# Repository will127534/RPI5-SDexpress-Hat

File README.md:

# RPI5-SDexpress-Hat

Basically a clone from my [CFE Hat](https://github.com/will127534/RPI5-CFE-Hat) project and just changed the CFexpress Socket to SDexpress.  

Hardware-wise SDexpress requires additional 1.8V DC-DC and I'm using PAM2306 here, note that you can see in the photo the FB resistors are actually missing, the board is design for the adjustable version but this chip has 1.8V/3.3V fixed output variant and in that case you can put the 0 ohm resistor and that's what I have in the photo.  

Raspberry Pi's software-wise it is the exact same as CFE hat, the FW on MCU is slightly different that for layout reasons I shifted the LED output to another port and the FW in HEX is in this repo. See this [Youtube](https://youtu.be/_K-CHcIZxTY) for the HAT in action (automount/manual unmount).

[Interactive BOM](https://htmlpreview.github.io/?https://github.com/will127534/RPI5-SDexpress-Hat/blob/main/bom/ibom.html) [(provided by InteractiveHtmlBom)
](https://github.com/openscopeproject/InteractiveHtmlBom) 

### Random notes
In general, I don't really see a point of using microSD express card: If you need external storage, M.2 SSD is cheaper; If you need removable storage, M.2 SSD in CFexpress Type B is cheaper.  

microSD express reading speed is indeed faster then microSD card, however it's writing speed is more about the same as high-end microSD express card (160~200MB/s). Now you might see some microSD express advertise for >200MB/s writing speed, but that is not *sustained* performance, similar to how NVMe SSD works, some microSD express have pSLC cache for higher burst write speed. So it make sense as a gaming storage but I don't see the point for camera recording or any type of high speed recording device given the pricing comparing to standard high-end microSD card / USB flash or M.2 SSDs. I actually waited for a while to see if there are cheaper options other then the Nintendo branded one but there is none. I'm guessing that there is a physical/power limit on how many NAND channel you can fit in microSD card format, which limits the sustained write performance because that is based on RAW NAND speed.  

Thermal-wise with and without external fan doesn't change the performance during the stress test that last for an hour, it does get a little bit warm but it is not hot at all so that is some good news. Something I didn't expect though is that there aren't a lot of options for the socket either, and there is no self-ejection options out there currently and it actually took me a lot of force to pull the card out.  For more card specific testing, see here for more: [https://github.com/geerlingguy/raspberry-pi-pcie-devices/issues/745](https://github.com/geerlingguy/raspberry-pi-pcie-devices/issues/745)

One last note: I won't do PCBA for this board because microSD express card is not there(Cost/Performance/Prevalent) yet, but this project is in MIT license so do whatever you want with this.

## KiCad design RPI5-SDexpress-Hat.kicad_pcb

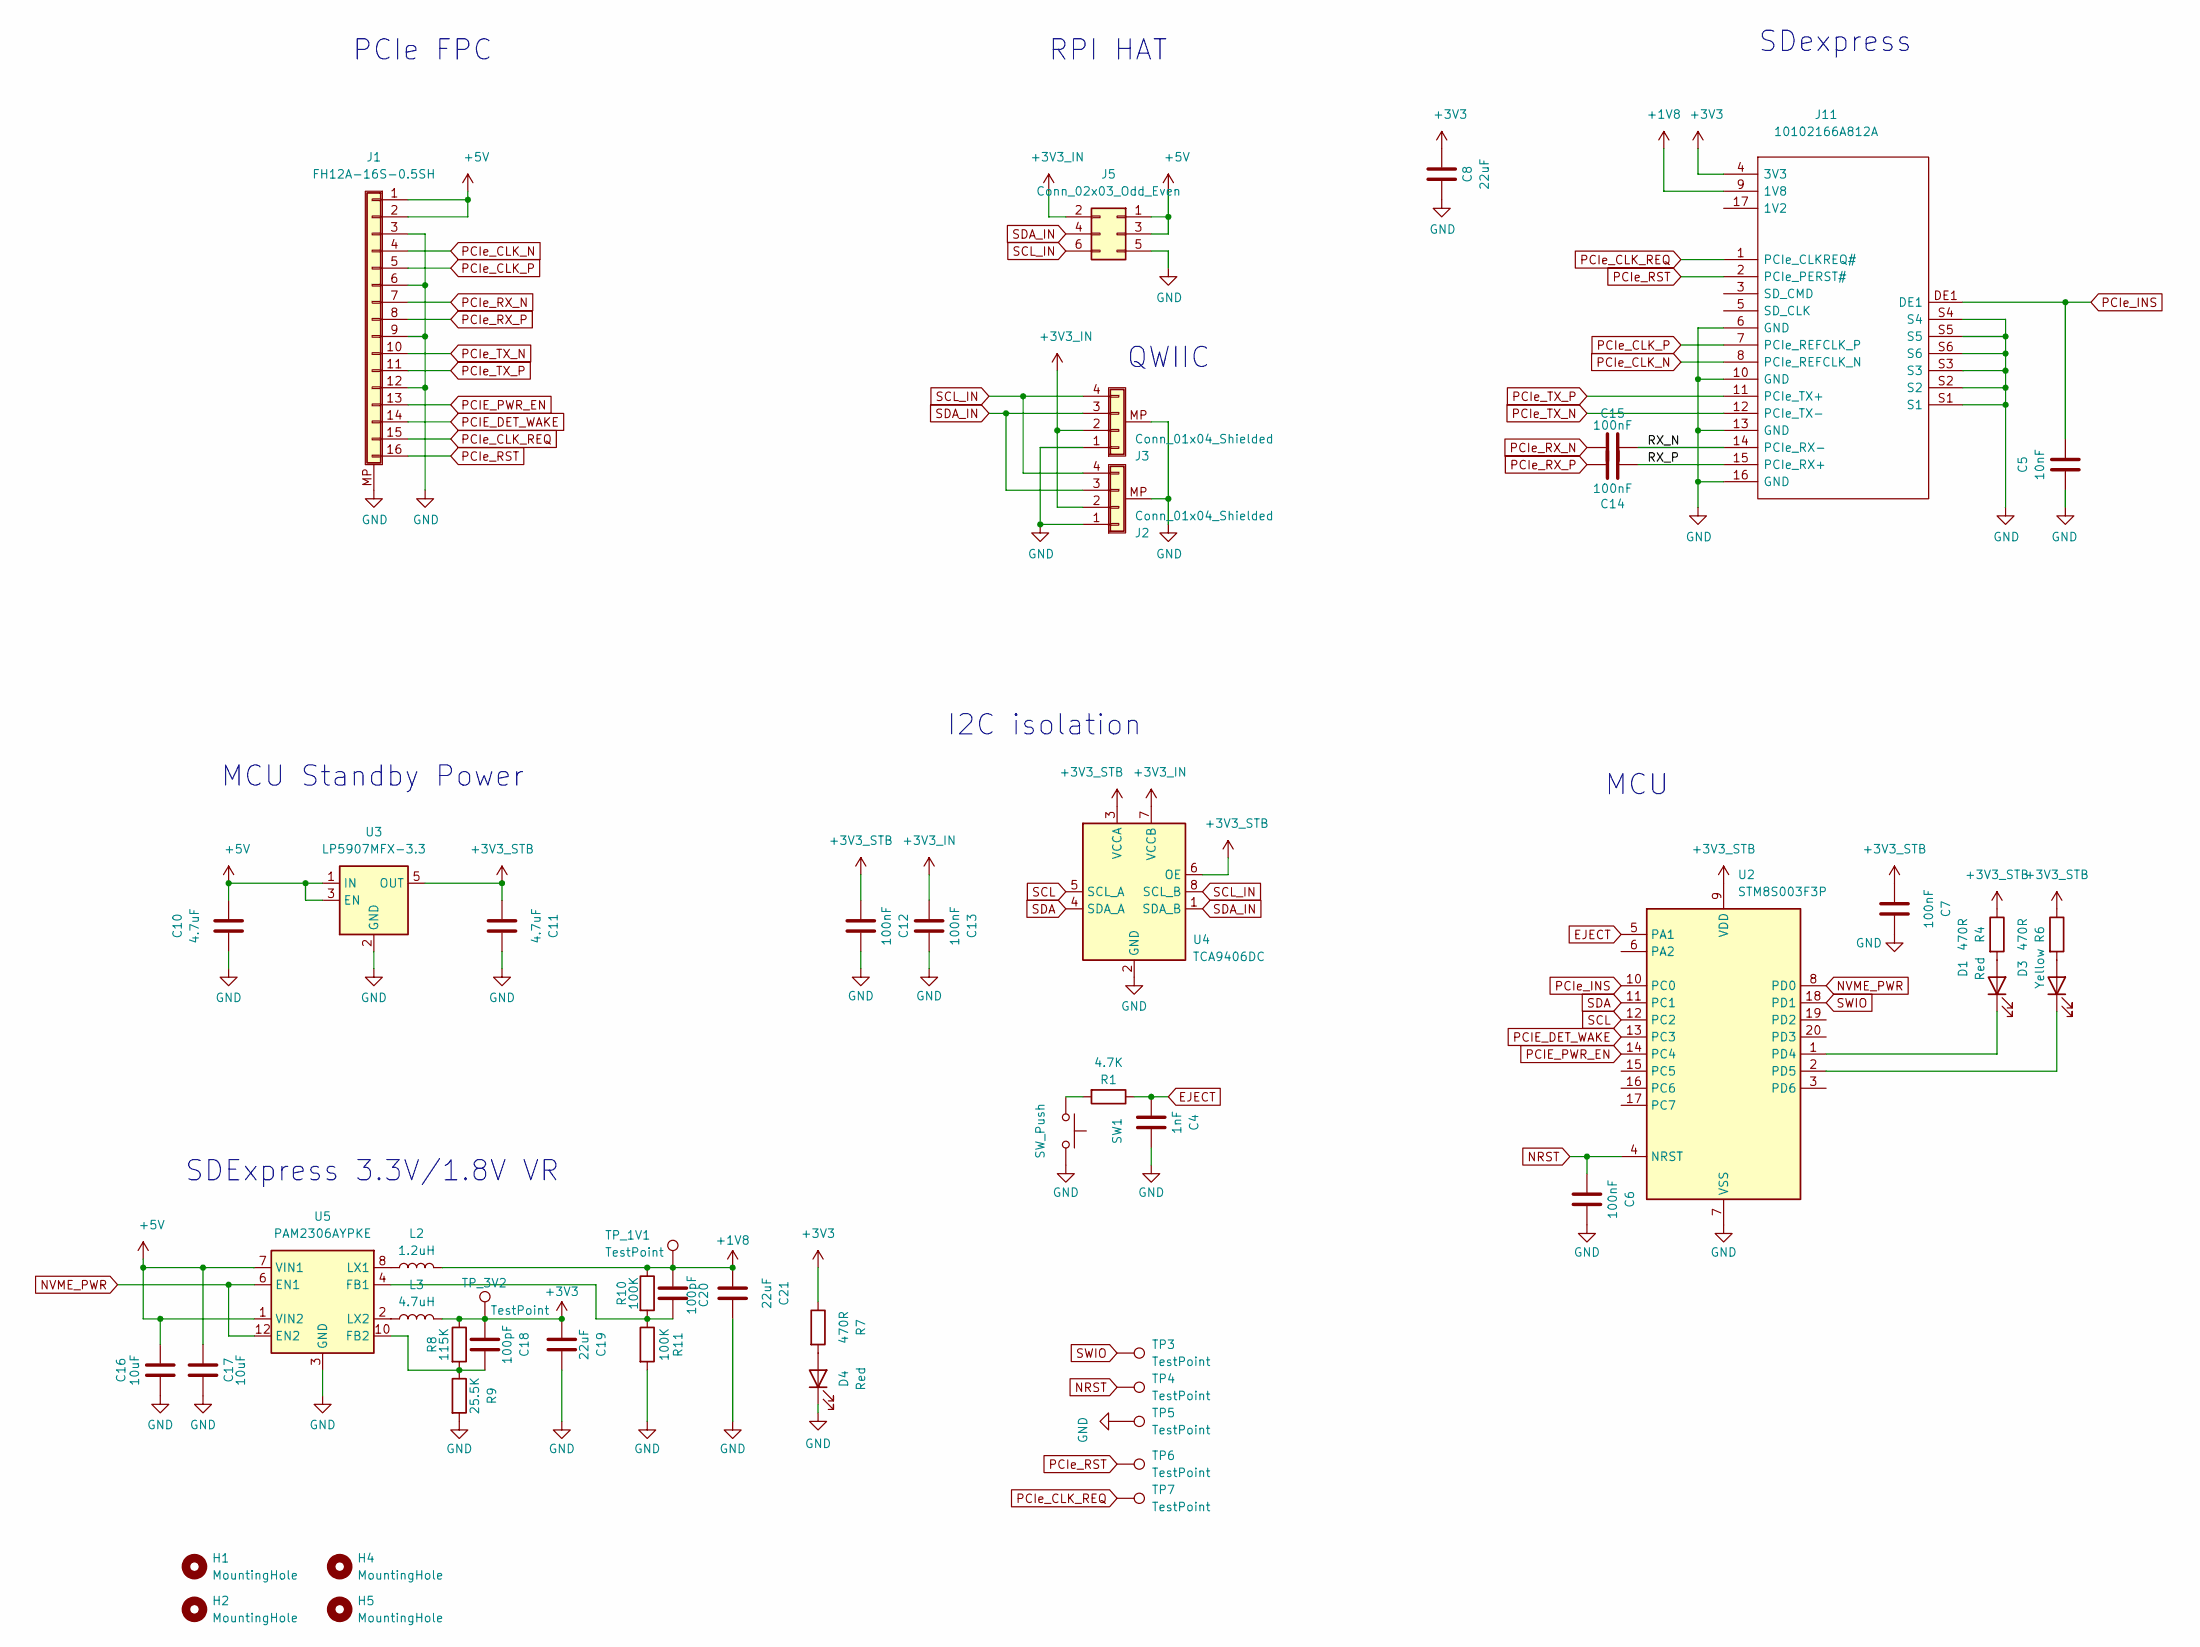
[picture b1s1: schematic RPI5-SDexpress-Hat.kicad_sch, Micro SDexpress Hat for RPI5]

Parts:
C4: 1nF; C_0402_1005Metric
C5: 10nF; C_0402_1005Metric
C6, C7, C12, C13, C14, C15: 100nF; C_0402_1005Metric
C8: 22uF; C_0805_2012Metric
C10, C11: 4.7uF; C_0603_1608Metric
C16, C17: 10uF; C_0603_1608Metric
C18, C20: 100pF; C_0402_1005Metric
C19, C21: 22uF; C_0603_1608Metric
D1, D4: Red; LED_0603_1608Metric
D3: Yellow; LED_0603_1608Metric
H1, H2, H4, H5: MountingHole; MountingHole_2.7mm_M2.5
J1: FH12A-16S-0.5SH; Hirose_FH12-16S-0.5SH_1x16-1MP_P0.50mm_Horizontal
J2, J3: Conn_01x04_Shielded; JST_SH_SM04B-SRSS-TB_1x04-1MP_P1.00mm_Horizontal
J5: Conn_02x03_Odd_Even; PinSocket_2x03_P2.54mm_Vertical
J11: 10102166A812A; Manufacturer_Part_Number 10102166A812A
L2: 1.2uH; L_Vishay_IHLP-1212
L3: 4.7uH; L_Vishay_IHLP-1212
R1: 4.7K; R_0402_1005Metric
R4, R6, R7: 470R; R_0402_1005Metric
R8: 115K; R_0402_1005Metric
R9: 25.5K; R_0402_1005Metric
R10, R11: 100K; R_0402_1005Metric
SW1: SW_Push; Panasonic_EVQPUM_EVQPUD
TP3, TP4, TP5, TP6, TP7: TestPoint; TestPoint_Pad_D1.0mm
TP_1V1, TP_3V2: TestPoint; TestPoint_Pad_D1.0mm
U2: STM8S003F3P; TSSOP-20_4.4x6.5mm_P0.65mm
U3: LP5907MFX-3.3; SOT-23-5
U4: TCA9406DC; TCA9406DCUR
U5: PAM2306AYPKE; WDFN-12-1EP_3x3mm_P0.45mm_EP1.7x2.5mm

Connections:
+1V8: C20.1, C21.1, J11.9 (1V8), L2.2, R10.1, TP_1V1.1
+3V3: C8.2, C18.1, C19.1, J11.4 (3V3), L3.2, R7.1, R8.1, TP_3V2.1
+3V3_IN: C13.1, J2.2, J3.2, J5.2, U4.7 (VCCB)
+3V3_STB: C7.1, C11.1, C12.1, R4.1, R6.1, U2.9 (VDD), U3.5 (OUT), U4.3 (VCCA), U4.6 (OE)
+5V: C10.2, C16.2, C17.2, J1.1, J1.2, J5.1, J5.3, U3.1 (IN), U3.3 (EN), U5.1 (VIN2), U5.7 (VIN1)
/RX_N: C15.2, J11.14 (PCIe_RX-)
/RX_P: C14.2, J11.15 (PCIe_RX+)
EJECT: C4.1, R1.1, U2.5 (PA1)
GND: C4.2, C5.2, C6.2, C7.2, C8.1, C10.1, C11.2, C12.2, C13.2, C16.1, C17.1, C19.2, C21.2, D4.1 (K), J1.3, J1.6, J1.9, J1.12, J1.MP (Shield), J2.1, J2.MP (Shield), J3.1, J3.MP (Shield), J5.5, J11.6 (GND), J11.10 (GND), J11.13 (GND), J11.16 (GND), J11.S1, J11.S2, J11.S3, J11.S4, J11.S5, J11.S6, R9.2, R11.2, SW1.1, TP5.1, U2.7 (VSS), U3.2 (GND), U4.2 (GND), U5.3 (GND), U5.9 (GND), U5.13 (GND)
NRST: C6.1, TP4.1, U2.4 (NRST)
NVME_PWR: U2.8 (PD0), U5.6 (EN1), U5.12 (EN2)
unnamed: D1.2 (A), R4.2
unnamed: D1.1 (K), U2.1 (PD4)
unnamed: D3.2 (A), R6.2
unnamed: D3.1 (K), U2.2 (PD5)
unnamed: D4.2 (A), R7.2
unnamed: R1.2, SW1.2
unnamed: C20.2, R10.2, R11.1, U5.4 (FB1)
unnamed: C18.2, R8.2, R9.1, U5.10 (FB2)
unnamed: L2.1, U5.8 (LX1)
unnamed: L3.1, U5.2 (LX2)
PCIE_DET_WAKE: J1.14, U2.13 (PC3)
PCIE_PWR_EN: J1.13, U2.14 (PC4)
PCIe_CLK_N: J1.4, J11.8 (PCIe_REFCLK_N)
PCIe_CLK_P: J1.5, J11.7 (PCIe_REFCLK_P)
PCIe_CLK_REQ: J1.15, J11.1 (PCIe_CLKREQ#), TP7.1
PCIe_INS: C5.1, J11.DE1, U2.10 (PC0)
PCIe_RST: J1.16, J11.2 (PCIe_PERST#), TP6.1
PCIe_RX_N: C15.1, J1.7
PCIe_RX_P: C14.1, J1.8
PCIe_TX_N: J1.10, J11.12 (PCIe_TX-)
PCIe_TX_P: J1.11, J11.11 (PCIe_TX+)
SCL: U2.12 (PC2), U4.5 (SCL_A)
SCL_IN: J2.4, J3.4, J5.6, U4.8 (SCL_B)
SDA: U2.11 (PC1), U4.4 (SDA_A)
SDA_IN: J2.3, J3.3, J5.4, U4.1 (SDA_B)
SWIO: TP3.1, U2.18 (PD1)

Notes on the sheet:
MCU
QWIIC
PCIe FPC
MCU Standby Power
I2C isolation
SDexpress
SDExpress 3.3V/1.8V VR
RPI HAT

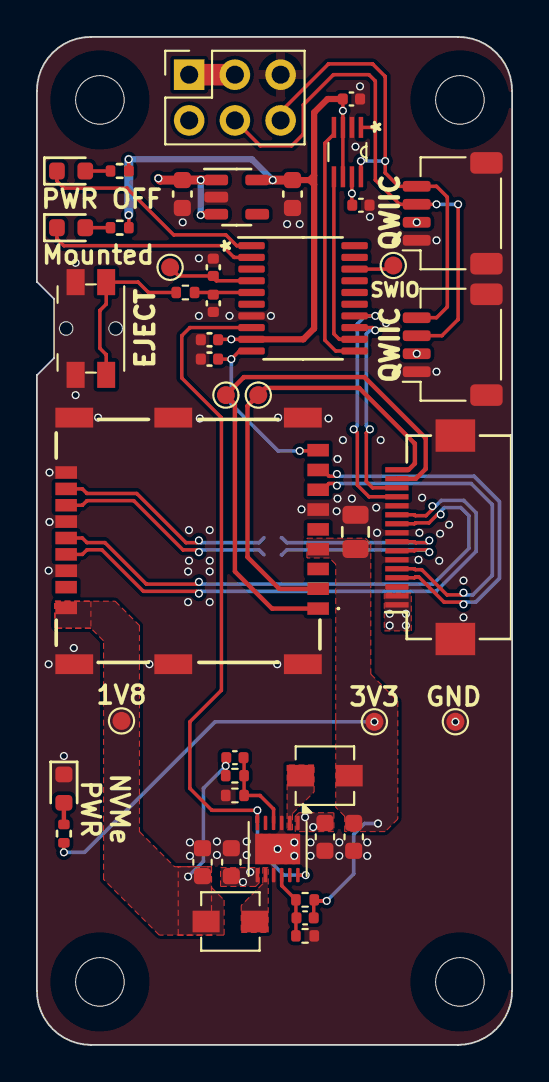
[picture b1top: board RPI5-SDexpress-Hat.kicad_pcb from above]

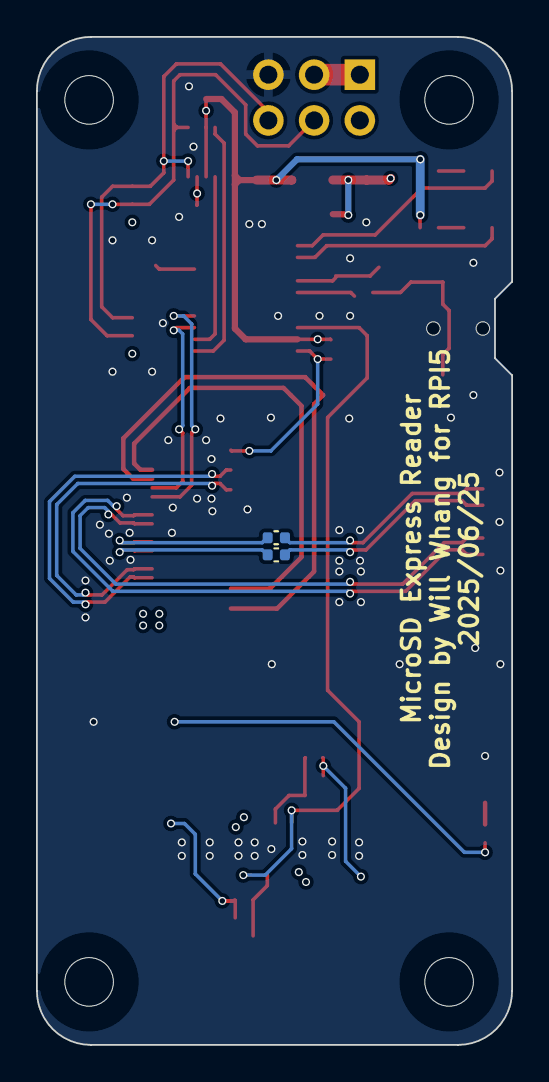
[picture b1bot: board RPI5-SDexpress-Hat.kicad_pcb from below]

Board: 4 copper layers, 26.4 x 56.0 mm, 51 parts (2 on the bottom side), 37 nets.

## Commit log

2025-07-26 init
2025-07-26 Adding BOM, clean up SCH, update FPC connector BOM
